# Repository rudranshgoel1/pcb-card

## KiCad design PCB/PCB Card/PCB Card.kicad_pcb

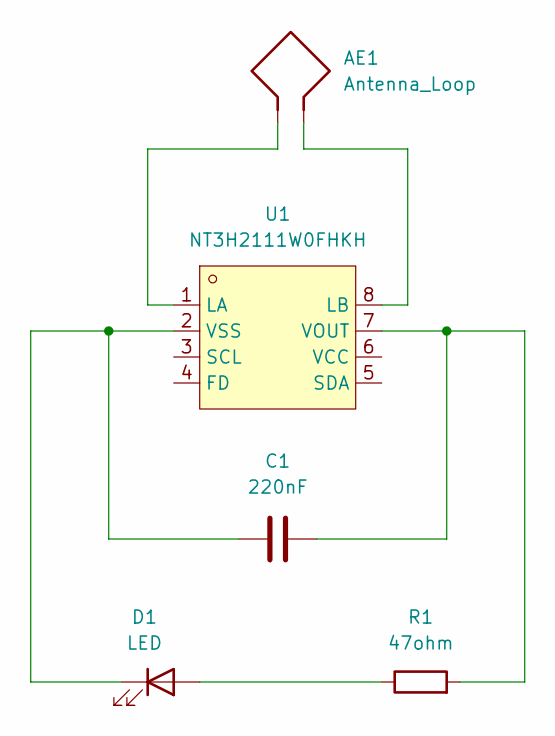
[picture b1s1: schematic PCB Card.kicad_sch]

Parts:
AE1: Antenna_Loop; NFC_30x30_N5_Custom_YOLO_Mode
C1: 220nF; C_0201_0603Metric
D1: LED; LED_0805_2012Metric
R1: 47ohm; R_0201_0603Metric
U1: NT3H2111W0FHKH; XQFN-8_L1.6-W1.6-P0.50-BL_NT3H2111W0FHKH; LCSC Part C710403

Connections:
unnamed: D1.2 (A), R1.1
unnamed: C1.1, D1.1 (K), U1.2 (VSS)
unnamed: AE1.1, U1.1 (LA)
unnamed: AE1.2, U1.8 (LB)
unnamed: C1.2, R1.2, U1.7 (VOUT)

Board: 2 copper layers, 5 parts (0 on the bottom side), 5 nets, no tracks yet.
